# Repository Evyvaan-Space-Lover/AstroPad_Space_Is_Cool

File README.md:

# AstroPad 

A space-themed 4-key macropad built using the Seeeduino XIAO, designed to bring astronomy, chaos, and peak productivity together.

> Why settle for volume controls when you can have a dedicated Bruh button?

---

## Features

-  **Stellarium Launcher** – Instantly open an interactive sky map.
-  **ISS Tracker** – Check the International Space Station's location with a single press.
-  **Bruh Button** – Play the legendary Bruh sound effect.
-  **NASA APOD** – Open NASA's Astronomy Picture of the Day.

### Bonus
- 0.91" OLED display support (planned)
-  Custom-designed PCB
-  Custom 3D-printed case
-  Mechanical switch support

---

## Hardware

| Component | Part |
|------------|-------|
| Microcontroller | Seeeduino XIAO (SAMD21) |
| Switches | 4 × MX-compatible mechanical switches |
| Display | 0.91" I²C OLED (SSD1306) |
| Case | Custom-designed 3D printed enclosure |
| Plate | Custom switch plate |
| Firmware | KMK Firmware |

---

## Schematic Overview

### Switch Connections

| Switch | XIAO Pin |
|---------|-----------|
| SW1 | D0 |
| SW2 | D1 |
| SW3 | D2 |
| SW4 | D3 |

### OLED Connections

| OLED Pin | XIAO Pin |
|-----------|-----------|
| VCC | 3V3 |
| GND | GND |
| SDA | D4 |
| SCL | D5 |

---

## Keymap

| Key | Action |
|------|---------|
|  SW1 | Open Stellarium |
|  SW2 | Open ISS Tracker |
|  SW3 | Play Bruh sound effect |
|  SW4 | Open NASA APOD |

---

## Software

AstroPad works by sending keyboard shortcuts using KMK firmware.

These shortcuts are intercepted on the host computer using AutoHotkey.

### AutoHotkey Bindings

| Shortcut | Action |
|-----------|---------|
| Ctrl + Alt + S | Open Stellarium |
| Ctrl + Alt + I | Open ISS Tracker |
| Ctrl + Alt + B | Play Bruh sound |
| Ctrl + Alt + N | Open NASA APOD |

Example AutoHotkey script:

```ahk
^!s::{
    Run "https://stellarium-web.org/"
}

^!i::{
    Run "https://spotthestation.nasa.gov/"
}

^!n::{
    Run "https://apod.nasa.gov/apod/astropix.html"
}

^!b::{
    SoundPlay "C:\Path\To\bruh.mp3"
}
```

---

## Firmware

AstroPad uses **KMK Firmware** running on CircuitPython.

The firmware is responsible for sending the keyboard shortcuts corresponding to each key.

OLED functionality will be implemented once the hardware arrives.

---

## 3D Printed Case

The enclosure was custom-designed in Fusion 360.

Features include:

- USB access cutout
- Mechanical switch support
- Dedicated OLED mounting area
- Compact footprint
- Space for future upgrades

---

## Project Structure

```
AstroPad/
├── PCB/
│   ├── AstroPad.kicad_sch
│   ├── AstroPad.kicad_pcb
│   └── Gerbers.zip
├── Case/
│   ├── AstroPad.f3d
│   ├── AstroPad.stl
│   └── Plate.dxf
├── Firmware/
│   └── code.py
├── Scripts/
│   └── AstroPad.ahk
└── README.md
```

---

## Future Improvements

- OLED status display
- ISS information display
- Animated graphics
- Multiple layers and modes
- Additional space-themed macros
- Integration with astronomy software APIs

---

## Inspiration

Most macropads focus on productivity.

AstroPad focuses on **space, curiosity, and occasionally pressing a dedicated Bruh button at the worst possible moment**.

---

## Status

```
PCB Design       ██████████ 100%
Case Design      ██████████ 100%
Plate Design     ██████████ 100%
Firmware         ███████░░░ 70%
OLED Features    ██░░░░░░░░ 20%
Sanity           ░░░░░░░░░░ 0%
```

---

Built by **Evyvaan Singh**.

*"The universe is under no obligation to make sense to you."*  
— Neil deGrasse Tyson

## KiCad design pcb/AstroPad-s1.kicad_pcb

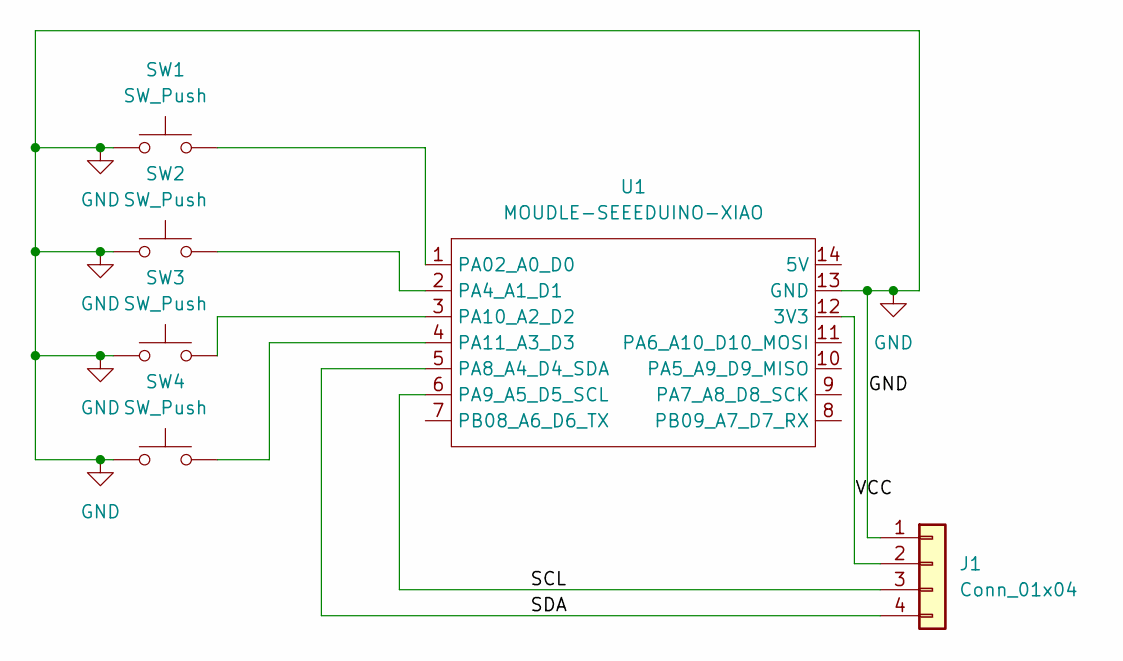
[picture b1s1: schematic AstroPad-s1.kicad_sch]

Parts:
J1: Conn_01x04; PinHeader_1x04_P2.54mm_Vertical
SW1, SW2, SW3, SW4: SW_Push; SW_Cherry_MX_1.00u_PCB
U1: MOUDLE-SEEEDUINO-XIAO; XIAO-Generic-Hybrid-14P-2.54-21X17.8MM

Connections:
/SCL: J1.3, U1.6 (PA9_A5_D5_SCL)
/SDA: J1.4, U1.5 (PA8_A4_D4_SDA)
/VCC: J1.2, U1.12 (3V3)
GND: J1.1, SW1.1, SW2.1, SW3.1, SW4.1, U1.13 (GND)
unnamed: SW1.2, U1.1 (PA02_A0_D0)
unnamed: SW2.2, U1.2 (PA4_A1_D1)
unnamed: SW3.2, U1.3 (PA10_A2_D2)
unnamed: SW4.2, U1.4 (PA11_A3_D3)

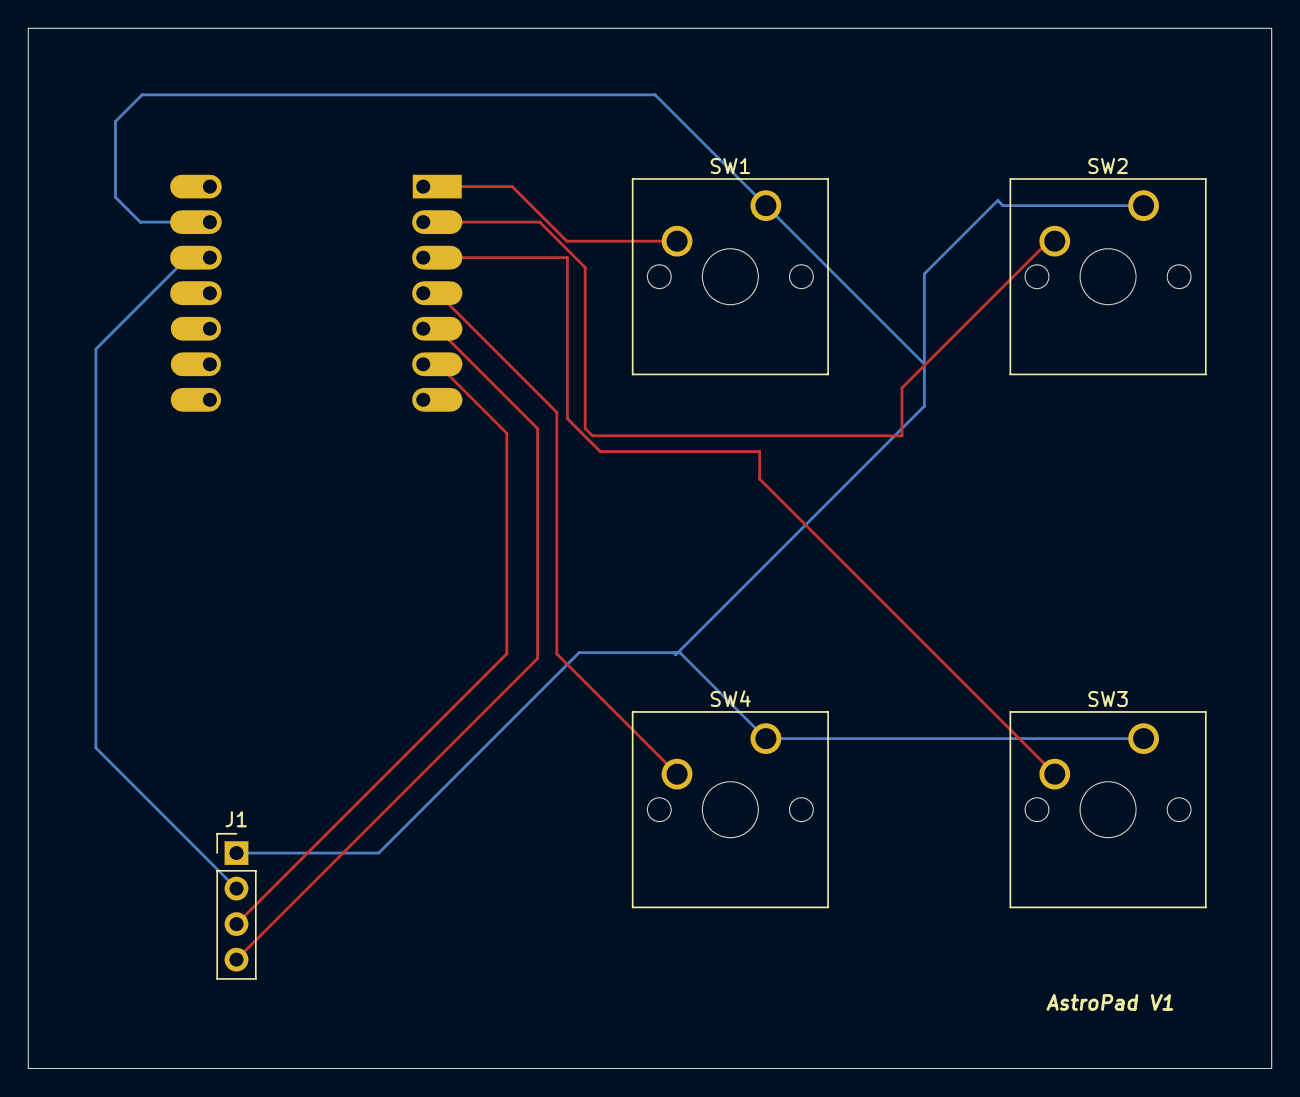
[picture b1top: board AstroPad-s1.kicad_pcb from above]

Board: 2 copper layers, 88.9 x 74.4 mm, 6 parts (1 on the bottom side), 8 nets.

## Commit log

2026-06-14 Ceated the repository
